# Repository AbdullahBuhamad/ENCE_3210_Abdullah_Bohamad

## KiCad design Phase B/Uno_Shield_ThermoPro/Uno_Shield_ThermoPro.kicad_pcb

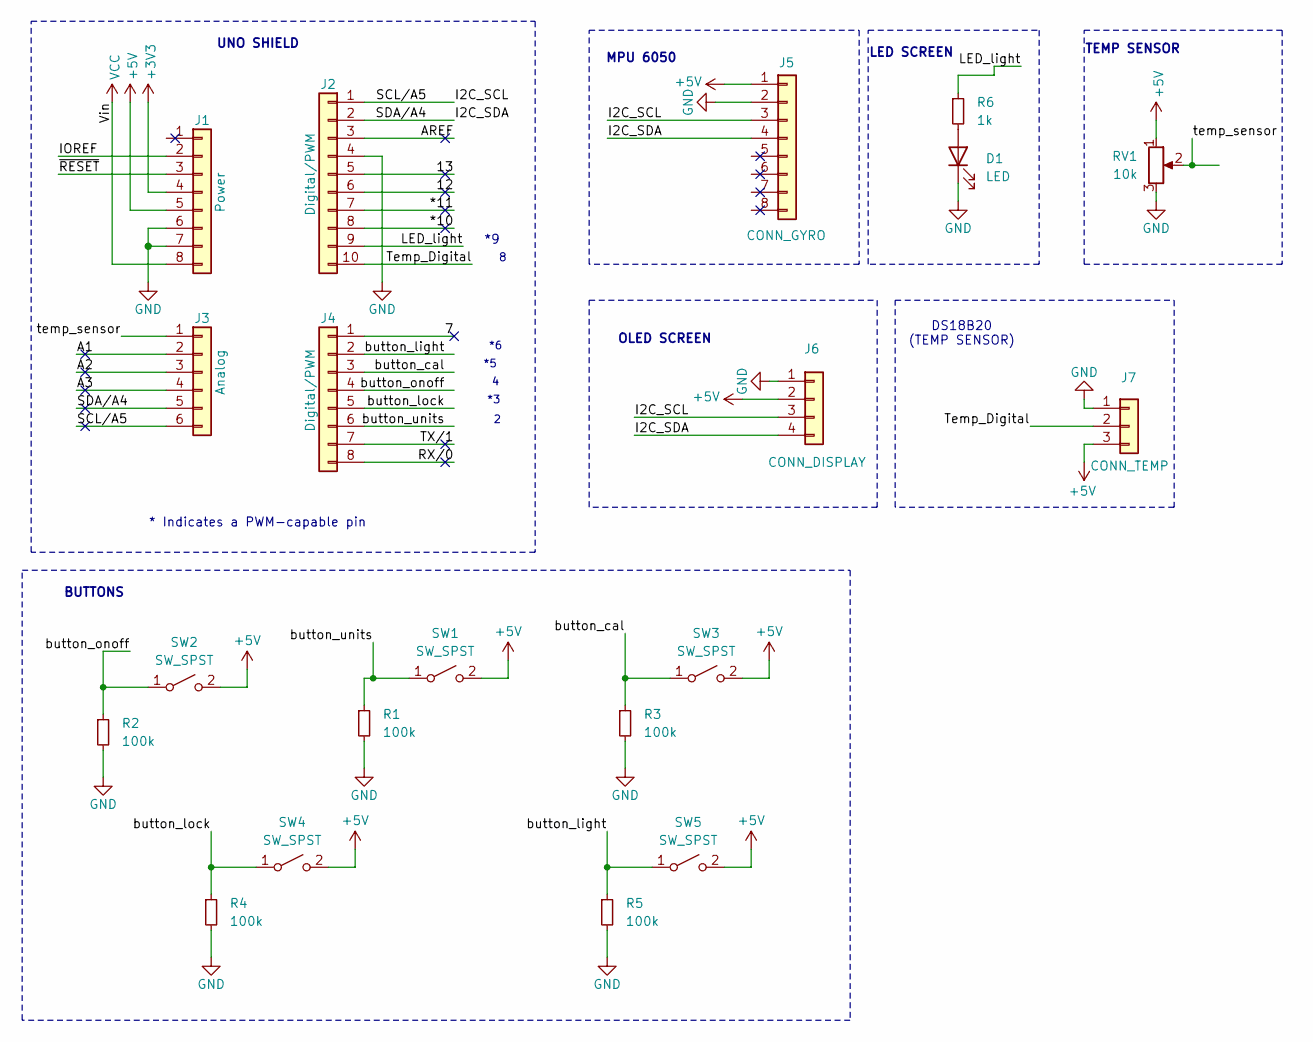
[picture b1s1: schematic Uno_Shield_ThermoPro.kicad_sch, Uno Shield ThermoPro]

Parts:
D1: LED; LED_D5.0mm
J1: Power; PinSocket_1x08_P2.54mm_Vertical
J2: Digital/PWM; PinSocket_1x10_P2.54mm_Vertical
J3: Analog; PinSocket_1x06_P2.54mm_Vertical
J4: Digital/PWM; PinSocket_1x08_P2.54mm_Vertical
J5: CONN_GYRO; PinSocket_1x08_P2.54mm_Vertical
J6: CONN_DISPLAY; PinSocket_1x04_P2.54mm_Vertical
J7: CONN_TEMP; JST_XH_B3B-XH-A_1x03_P2.50mm_Vertical
R1, R2, R3, R4, R5: 100k; R_Axial_DIN0411_L9.9mm_D3.6mm_P15.24mm_Horizontal
R6: 1k; R_Axial_DIN0411_L9.9mm_D3.6mm_P15.24mm_Horizontal
RV1: 10k; Potentiometer_Bourns_3386P_Vertical
SW1, SW2, SW3, SW4, SW5: SW_SPST; SW_PUSH_6mm

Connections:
+3V3: J1.4
+5V: J1.5, J5.1, J6.2, J7.3, RV1.1, SW1.2 (B), SW2.2 (B), SW3.2 (B), SW4.2 (B), SW5.2 (B)
/7: J4.1
/12: J2.6
/13: J2.5
/*10: J2.8
/*11: J2.7
/A1: J3.2
/A2: J3.3
/A3: J3.4
/AREF: J2.3
/I2C_SCL: J2.1, J3.6, J5.3, J6.3
/I2C_SDA: J2.2, J3.5, J5.4, J6.4
/IOREF: J1.2
/LED_light: J2.9, R6.1
/RX/0: J4.8
/TX/1: J4.7
/Temp_Digital: J2.10, J7.2
/button_cal: J4.3, R3.1, SW3.1 (A)
/button_light: J4.2, R5.1, SW5.1 (A)
/button_lock: J4.5, R4.1, SW4.1 (A)
/button_onoff: J4.4, R2.1, SW2.1 (A)
/button_units: J4.6, R1.1, SW1.1 (A)
/temp_sensor: J3.1, RV1.2
/~RESET: J1.3
GND: D1.1 (K), J1.6, J1.7, J2.4, J5.2, J6.1, J7.1, R1.2, R2.2, R3.2, R4.2, R5.2, RV1.3
unnamed: D1.2 (A), R6.2
VCC: J1.8

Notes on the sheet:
OLED SCREEN
TEMP SENSOR
UNO SHIELD
MPU 6050
LED SCREEN
DS18B20 (TEMP SENSOR)
* Indicates a PWM-capable pin
BUTTONS

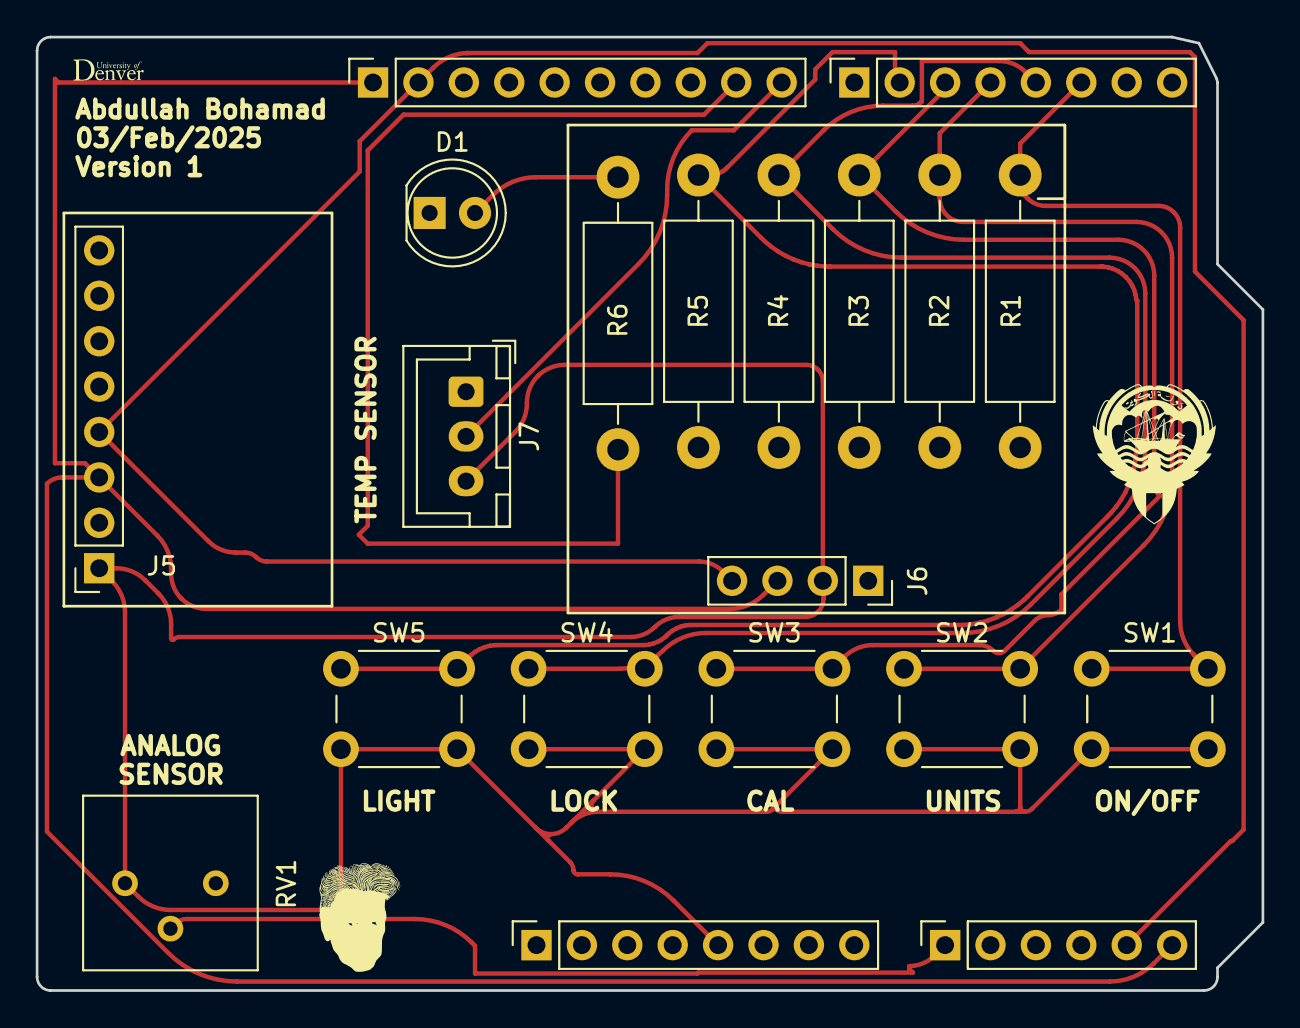
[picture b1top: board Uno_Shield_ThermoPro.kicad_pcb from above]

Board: 2 copper layers, 68.6 x 53.3 mm, 20 parts (0 on the bottom side), 13 nets.

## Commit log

2025-01-10 Lab 1
    Lab 1 Ex1
2025-01-10 Lab1_Ex1
2025-01-10 Create Lab 1
2025-01-15 Lab 1
2025-01-21 Lab 2
